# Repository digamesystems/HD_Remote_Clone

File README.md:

# HD Platinum Remote Clone

|  |  |
|:---:|:---:|
| Assembled (CAD render) | Exploded (CAD render) |

*The board inside, rev 1 (KiCad render). More in [hardware/](hardware/README.md).*

A DIY replacement for the handheld remote used with Hunter Douglas **Platinum Technology** motorized shades (the 2013-era system, before PowerView). It's built on an ESP32 with an IR LED (plus an IR receiver on the breadboard version, for capturing the original remote) and an nRF24L01+ 2.4 GHz radio.

> Personal hobby project. Not affiliated with or endorsed by Hunter Douglas. "Hunter Douglas", "Platinum" and "PowerView" are their trademarks and are used here only to say what this works with.

## Goal

Replace a degraded original remote with a homemade one that can:

- **Point and press (IR, 40 kHz):** control a single shade by aiming at its sensor eye. This is the arrows' default mode (red LED).
- **Group control (RF, 2.4 GHz):** pressing a group key (1–4 or ALL) opens a short window in which the arrows control that group over RF (green LED), as on the original.
- Run on batteries, sleeping deeply between presses and waking on a button press.

The protocols aren't documented, so the first phase was reverse engineering. This repo's firmware is the toolkit for that: it captures, dumps and replays IR, tests, scans and sniffs nRF24, and now drives shades on its own (IR with the RF wake, group commands, and pairing under its own ID). The next phase is the handheld: a custom PCB (designed, not yet built) and its firmware.

## Where things are

| Want to… | Go to |
|---|---|
| **Build one and control your shades** | **[docs/BUILD.md](docs/BUILD.md)** |
| Understand the IR codes | [docs/IR_PROTOCOL.md](docs/IR_PROTOCOL.md) |
| Understand the 2.4 GHz RF frames and pairing | [docs/RF_PROTOCOL.md](docs/RF_PROTOCOL.md) |
| See what is still unknown | [docs/RESEARCH.md](docs/RESEARCH.md) |
| See ideas beyond the stock remote | [docs/FEATURE_IDEAS.md](docs/FEATURE_IDEAS.md) |
| Run the firmware, see the serial commands and pin map | [docs/FIRMWARE.md](docs/FIRMWARE.md) |
| Wire the breadboard / nRF24 modules | [docs/WIRING.md](docs/WIRING.md) |
| Build the handheld | [docs/HARDWARE.md](docs/HARDWARE.md) (spec), [hardware/](hardware/README.md) (PCB), [hardware/enclosure/](hardware/enclosure/README.md) (case), [docs/BOM.md](docs/BOM.md), [docs/BRINGUP.md](docs/BRINGUP.md), [docs/COSTS.md](docs/COSTS.md) |
| Check the raw evidence | [captures/](captures/) (serial logs, logic-analyzer files; remote IDs redacted) |
| Test a change | [TESTING.md](TESTING.md) |

## Contributing

Hardware-independent logic belongs in `lib/hdcore/` with a host unit test; hardware-touching code goes in `src/`. Read [TESTING.md](TESTING.md) first. `include/hw_config.h` records what hardware is present on each board (breadboard, or the handheld PCB with `-e handheld`). Docs say what is confirmed and what is hypothesis; please keep it that way.

## Quick start

```
pio run -t upload         # breadboard (esp32dev)
pio device monitor        # 115200 baud, then type help
pio run -e handheld       # handheld PCB profile (builds; untested on hardware)
pio test -e native        # host unit tests, no hardware
```

Commands and pin map: [docs/FIRMWARE.md](docs/FIRMWARE.md).

## Status

| Stage | State |
|---|---|
| PlatformIO project, serial-menu firmware | ✅ builds |
| ESP32 board identified (DevKitC, WROOM-32D) | ✅ |
| IR protocol decoded (channel A: UP `0101`, DOWN `0110`; channel B: `1001` / `1010`), see [IR_PROTOCOL.md](docs/IR_PROTOCOL.md) | ✅ |
| IR transmit to a shade | ✅ works with our own RF wake, no original remote (2026-11-11); reliable at ~1 ft, range limited by IR aim/power. The shade sleeps after a few seconds, so the wake must keep coming through the press (2026-11-15) |
| nRF24 module screening (marked `NRF24L01+`, possibly clones) | ⏳ first module passes; rest to test |
| RF settings on our remotes | ✅ published settings confirmed by sniffing (2026-11-11) |
| RF wake frame for IR (`ID 01 00 80`) | ✅ sniffed from both remotes, see [RF_PROTOCOL.md](docs/RF_PROTOCOL.md) |
| RF transmit emulation | ✅ red-mode wake (`wake`, `send`) and group commands (`grp`): groups 1–4 and All, up and down (2026-11-11); group pairing under the clone's own ID (`pair`, 2026-11-12) |
| Handheld PCB (KiCad, [hardware/](hardware/README.md)) | ✅ schematic and layout complete, DRC/ERC clean; 5 assembled boards ordered from JLCPCB 2026-11-17, received 2026-11-25. ⏳ Bring-up under way: board 1 passes the unpowered, USB power and flashing stages; log in [docs/BRINGUP.md](docs/BRINGUP.md) |
| Enclosure (3D-printed clamshell, [hardware/enclosure/](hardware/enclosure/README.md)) | ✅ modelled, fit checks pass against the board; test print arrived 2026-11-20 and its values are in the model; the case order waits for the first board's measurements |
| Firmware pin profile for the PCB (`pio run -e handheld`) | ⏳ runs on board 1 (2026-11-25): serial menu, keys, A/B slider, radio and battery reading work (the voltage reads about 4.5 % high), and the board's keys move shades in group mode; indicator LED and IR not yet tested |
| Final remote: button UX, indicator LED, deep sleep, enclosure | ⏳ key logic written and host-tested, and running on the breadboard through the laptop keys (fw 0.9.11–0.9.12) and on the PCB through its own keys (fw 0.9.14); LED patterns and deep sleep still to be written |

## Technical approach
### What the original remote does

- **IR mode (red LED):** a proprietary IR code on a 40 kHz carrier, aimed at one shade. Pressing the opposite button stops movement.
- **RF mode (green LED):** an nRF24L01+ inside the remote. You select a group, then press OPEN or CLOSE within 5 s (we measured about 6.5 s; pressing a group key again restarts the window). Prior community work ([spitcool/hd-platinum-rf](https://github.com/spitcool/hd-platinum-rf), `docs/rf-protocol.md`, citing FCC filings, a register dump and SDR captures; and the [Arduino forum](https://forum.arduino.cc/t/nrf24l01-hack-on-hunter-douglas-shades/676940)) reports:

  | Parameter | Platinum handheld |
  |---|---|
  | Channels | 33, 52, 71 (2433 / 2452 / 2471 MHz), one packet per channel in rotation, for as long as the key is held |
  | Data rate | 2 Mbps |
  | Address | 3 bytes, `E7 E7 E7` (the nRF24 power-on default) |
  | Payload | 5 bytes, static: `ID0 ID1 MODE GROUP ACTION` |
  | CRC / auto-ack | CRC-16 / off |
  | Original TX power | about −6 dBm |

  - `ID0 ID1` identify the remote. Group commands are checked against the ID (a made-up ID gets no response), but the red-mode wake isn't (2026-11-12). Our two remotes have different IDs, and both work.
  - `MODE` is `20` with a group active, `01` for a red-mode press, and `30` / `31` for a setup-mode (pairing) add / remove. `GROUP` is `01/02/04/08` for groups 1–4, `FF` for All. `ACTION` is `A1` up held, `A2` down held, then `21` / `22` as a release tail; with the remote's A/B slider on B they are `A3` / `A4` and `23` / `24` (our sniff, 2026-11-25).
  - **A red-mode (IR) arrow press also sends RF:** `ID 01 00 80` while held, with no direction. The shade needs it before it will act on the IR. Our finding, 2026-11-11.
  - Example from the forum (another remote's ID): `03 C1 20 01 A1`, group 1 up.
  - Channel 7 / 1 Mbps, quoted in one forum thread, conflicts with this. spitcool's notes associate those settings with the later PowerView Pebble remote.
  - **Confirmed on both our remotes** by sniffing ch 33 (2026-11-11). Details in [RF_PROTOCOL.md](docs/RF_PROTOCOL.md).

Open questions and the reverse-engineering plan: [docs/RESEARCH.md](docs/RESEARCH.md).

## Hardware

Two targets. The **breadboard** was used for the reverse engineering and is what the [pin map](docs/FIRMWARE.md#pin-map) describes:

- **MCU:** ESP32-DevKitC with ESP32-WROOM-32D (PlatformIO `esp32dev`)
- **IR receive:** TSOP38238 (38 kHz part, fine for a 40 kHz remote at close range)
- **IR transmit:** TSAL6200 LED driven by an NPN transistor (2N2222) at ~100 mA pulses
- **RF:** nRF24L01+ module with a PCB antenna, 3.3 V supply and a 10 µF cap at the module

The **handheld PCB** (rev 1, DRC-clean; ordered from JLCPCB 2026-11-17, received 2026-11-25, in [bring-up](docs/BRINGUP.md)) has an ESP32-WROOM-32E, two TSAL6200 IR LEDs on constant-current sinks, no IR receiver, the nRF24 module in a low-profile 2×4 socket (Samtec SLW-104-01-G-D, with the module's header pins trimmed), seven keys plus a recessed SETUP button and an A/B channel slider, a red/green indicator LED seen through a light pipe, a LiPo cell charged over USB-C, and a USB-serial bridge for flashing and debugging. It lives in a 3D-printed clamshell case. See [docs/HARDWARE.md](docs/HARDWARE.md) (spec), [hardware/README.md](hardware/README.md) (layout status), [docs/BOM.md](docs/BOM.md) and [hardware/enclosure/](hardware/enclosure/README.md).

Pin map and firmware commands: [docs/FIRMWARE.md](docs/FIRMWARE.md). The handheld PCB uses a different pin map: see [docs/HARDWARE.md](docs/HARDWARE.md#pin-map-esp32-wroom-32e) and `include/pins.h`.

## Testing

```
pio test -e native                          # host unit tests, no hardware
pio test -e esp32dev_test --upload-port COM11    # on-device tests
```

See [TESTING.md](TESTING.md) for the three test tiers and the gate a release must pass.

## License

Copyright © 2026 John Price.

| Part | License |
|---|---|
| Firmware and tools (`src/`, `lib/`, `include/`, `test/`, `hardware/tools/`) | GNU General Public License, version 2 or (at your option) any later version (`GPL-2.0-or-later`). See [LICENSE](LICENSE). |
| Hardware design (`hardware/hd_remote/` KiCad files, `hardware/enclosure/` enclosure models) | CERN Open Hardware Licence v2, strongly reciprocal (`CERN-OHL-S-2.0`). See [hardware/LICENSE](hardware/LICENSE). |
| Documentation, captures and images (`docs/`, `captures/`, the READMEs) | Creative Commons Attribution-ShareAlike 4.0 (`CC-BY-SA-4.0`). See [docs/LICENSE](docs/LICENSE). |

Source files carry an `SPDX-License-Identifier` line. Third-party libraries keep their own licenses: [RF24](https://github.com/nRF24/RF24) (GPL-2.0) and [IRremoteESP8266](https://github.com/crankyoldgit/IRremoteESP8266) (LGPL-2.1). RF protocol facts credited to [spitcool/hd-platinum-rf](https://github.com/spitcool/hd-platinum-rf) are cited, not copied.

## Related projects

Found through [spitcool's CREDITS.md](https://github.com/spitcool/hd-platinum-rf/blob/main/CREDITS.md), which records the wider lineage in detail. Links checked 2026-11-18.

**Have the Platinum App Bridge?** These control Platinum shades through the Bridge over your LAN (TCP port 522), with no radio hardware to build:

- [node-hunterdouglas](https://github.com/exPHAT/node-hunterdouglas): JavaScript client, the earliest of these
- [homebridge-hunterdouglas-platinum](https://github.com/schemers/homebridge-hunterdouglas-platinum): Apple HomeKit via Homebridge
- [aio-powerrise-api](https://pypi.org/project/aio-powerrise-api/): asynchronous Python client
- [smartthings-hunterdouglasplatinum](https://github.com/schwark/smartthings-hunterdouglasplatinum): SmartThings integration
- [Platinum Shade Vera plug-in](https://community.ezlo.com/t/hunter-douglas-platinum-bridge-app/187439?page=3): Vera/Ezlo forum thread

**RF research and tools:**

- [spitcool/hd-platinum-rf](https://github.com/spitcool/hd-platinum-rf): SDR-based protocol research and an ESP32 bridge; the source of our RF air settings
- [gr-nrf24-sniffer](https://github.com/kittennbfive/gr-nrf24-sniffer): GNU Radio nRF24 receiver for an SDR such as a HackRF; supports 2 Mbps and 3-byte addresses (its own docs call 3-byte addresses untested)
- [gr-nordic](https://github.com/BastilleResearch/gr-nordic): GNU Radio Nordic ShockBurst receiver/transmitter (built around 5-byte addresses)
- [NRF24_Sniffer](https://github.com/Yveaux/NRF24_Sniffer): promiscuous sniffing with an nRF24 module

**Other Platinum devices** (FCC IDs; descriptions from spitcool's notes): [UXURC4U](https://fccid.io/UXURC4U) handheld remote, [UXURC4U2](https://fccid.io/UXURC4U2) handheld remote (ours), [UXURC4U3](https://fccid.io/UXURC4U3) later handheld remote, [UXUWS4U](https://fccid.io/UXUWS4U) wall switch. Only the UXURC4U2 has been tested with this project.

**Not compatible:** Hunter Douglas says current PowerView remotes and accessories, such as the Pebble, use a different communication method from Platinum Technology products and can't control older shades ([FAQ](https://www.hunterdouglas.com/faqs/can-i-use-my-new-powerview-pebble-remote-to-operate-my-older-powerrise-shades)).

## References

- [NRF24L01+ hack on Hunter Douglas shades](https://forum.arduino.cc/t/nrf24l01-hack-on-hunter-douglas-shades/676940) (Arduino forum)
- [ESP8266 and NRF24L01+ Hunter Douglas Platinum Remote](https://forum.arduino.cc/t/esp8266-and-nrf24l01-hunter-douglas-platinum-remote/918887) (Arduino forum)
- [spitcool/hd-platinum-rf](https://github.com/spitcool/hd-platinum-rf): protocol research
- [Platinum Technology remote guide (PDF)](https://blindparts.com/wp-content/uploads/1970/01/Hunter-Douglas-Platinum-Technology-Remote-Control-Guide.pdf)
- [Bond forum: IR replay attempts / RF wake theory](https://forum.bondhome.io/t/hunterdouglas-powerrise-2-0-with-platinum-technology/3050)
- [AVS forum: automating PowerRise (2007)](https://www.avsforum.com/threads/automating-hunter-douglas-powerrise.852487/)

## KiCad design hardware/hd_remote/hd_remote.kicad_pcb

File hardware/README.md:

# Hardware

*Rev 1 as ordered 2026-11-17: KiCad 3D render, not a photo. Top side, front (IR) end at the right. Some 3D models are stand-ins (the IR LEDs render green, the indicator white).*

KiCad project for the handheld replacement remote: [`hd_remote/hd_remote.kicad_pro`](hd_remote/hd_remote.kicad_pro).

- **Tool:** KiCad 10 (the files open in 9.0 or newer).
- **Spec:** [docs/HARDWARE.md](../docs/HARDWARE.md) holds the design decisions, pin map, power budget and open questions. Change the spec first, then the schematic.
- **Breadboard wiring** (the DevKitC prototype this board replaces): [docs/WIRING.md](../docs/WIRING.md).

## Status

| Sheet | State |
|---|---|
| Power and USB (`power_usb.kicad_sch`) | complete, drafted 2026-11-12. Values and *verify* items: [docs/HARDWARE.md](../docs/HARDWARE.md#schematic-power-and-usb-sheet-draft-2026-11-12) |
| MCU (`mcu.kicad_sch`) | complete, drafted 2026-11-12: [docs/HARDWARE.md](../docs/HARDWARE.md#schematic-mcu-sheet-draft-2026-11-12) |
| IR (`ir.kicad_sch`) | complete, drafted 2026-11-12: [docs/HARDWARE.md](../docs/HARDWARE.md#schematic-ir-sheet-draft-2026-11-12) |
| nRF24 (`nrf24.kicad_sch`), Buttons and LEDs (`ui.kicad_sch`) | complete, drafted 2026-11-12: [docs/HARDWARE.md](../docs/HARDWARE.md#schematic-nrf24-and-buttonsleds-sheets-draft-2026-11-12) |
| Test and debug (`test.kicad_sch`) | complete, drafted 2026-11-12: [docs/HARDWARE.md](../docs/HARDWARE.md#test-points-2026-11-12). Test points on nets local to other sheets live on those sheets |
| Layout | started 2026-11-13: all 109 footprints and 82 nets pulled in from the schematic (DRC schematic parity: 0 issues), parked below the sheet. Board outline (145.45 × 40.45 mm) from `docs/images/enclosure/enclosure_pcb_outline.dxf`, board centre at (100, 80) mm on the sheet, front end (IR LEDs) at +X, top view not mirrored; M2 holes H601–H604 placed and locked at (±61, ±15.5) mm. Design rules: KiCad defaults, inside JLC's standard process (0.2 mm track/clearance, 0.3 mm min hole). **U201 is modified locally:** its 12 ground-pad vias are 0.3 mm drill / 0.6 mm pad (the library has 0.2 mm, below JLC's standard drill), so DRC reports one expected `lib_footprint_mismatch`; don't update U201 from the library. **Case-fixed parts placed and locked** (2026-11-13) from `hardware/enclosure` coordinates: 7 key switches, SETUP (underside, 22 mm from the front, 10 mm right of centre), IR LEDs D303/D304, indicator D501, A/B SW509, USB-C J101, battery JST J102, ESP32 U201, nRF24 socket J401. Keep-outs: battery (named rule area `Battery` + custom rule in `hd_remote.kicad_dru`: no THT component pins over the cell; plated vias allowed), bottom side under each key's support pad, screw heads/standoffs, and the nRF24 module's PCB antenna. Expected DRC: silkscreen clipped at the board edge where the LEDs, USB-C and JST overhang it. **Rest of the parts: first-pass placement** (2026-11-13, scripted, unlocked): each part at the nearest free spot to the pads it connects to, ICs first; no courtyard or keep-out errors. It proves the fit, not a final layout: move decoupling caps to their pins (C201 especially), tighten the USB pair, tidy the silkscreen. **Check before routing:** J401's pin-1 orientation against a real module. **First-draft placement complete** (2026-11-13, by hand): every part on the board, DRC errors 0. **Routing setup** (2026-11-13): net classes Power 0.5 mm (+3V3, VBUS, NRF_VCC) and HighCurrent 0.6 mm (VBAT, VBAT_BATT, VBAT_JP, IR_K1/K2, IR_E1/E2; 0.6 matches the SOT-23 pads and carries well over the ~300 mA peak), Default 0.2 mm; GND pour on B.Cu over the whole board (0.3 mm clearance, thermal reliefs), kept out of both antenna keep-outs and the screw heads. **ESP32 rotated 180°** (2026-11-13): antenna end at the −Y edge, so its key/RTC pins face the keys and its SPI/UART pins face the back (see docs/HARDWARE.md, Layout notes); 21 parts re-homed (EN, battery-sense and 3V3 decoupling to the new pin positions; BOOT, J601, JP101/Q103, charger caps and the underside test pads out of the module's new footprint and antenna keep-out); case model updated, 51/51 checks pass. **Power path added** (2026-11-13, Microchip AN1149): D102 STPS1H100AY, Q104 AO3401A, R114 100 kΩ, TP102; loads (LDO, IR LEDs) moved from VBAT to the new VSYS rail; schematic ERC 0, board synced (parity 0), new parts placed by the charger. **Routing complete** (2026-11-14, by hand): DRC 0 errors, **0 unconnected**, schematic parity clean; ERC 0. Expected DRC warnings only: silkscreen clipped at the board edge (J101, J102, D303, D304); the other silkscreen warnings were tidied 2026-11-16; and U201's `lib_footprint_mismatch`. Decisions made while routing: the nRF24 antenna rule area bans ground fill and pads but allows tracks and vias (docs/HARDWARE.md, nRF24 socket); GND pour on B.Cu only, stitched; **VSYS** runs from D102/Q104 along the board's north edge to the IR stage, and U104 is fed from there along the existing y 85.5 run (about 200 mm of 0.6 mm track to the LDO: a few mV of drop, 20–30 mV of IR-burst ripple at its input); +3V3 to the nRF supply (FB401) along the top edge; **SW202 has "duplicate pad numbers are jumpers" set** (its two IO0 pads are joined inside the switch, and the second pad sits beyond a +3V3 track). Set it on the schematic's `Switch:SW_Push` symbol in `mcu.kicad_sch` (so SW201 has it too), not just on the footprint: Update PCB from Schematic copies the symbol's setting and reset the footprint-only fix on 2026-11-15; a small GND patch near SW202 is tied to the main plane through SW202's GND pad. **Since then (2026-11-16):** silkscreen tidied; board STEP exported and clash-checked against the case (61 checks); **J401 footprint fixed** (KiCad's `PinSocket_2x04` mirrors the pad order, so the module's pins were swapped between columns; now `PinHeader_2x04` at the same holes, re-routed); the ground pour opened around J401's GND pin (NRF_IRQ_OPT moved to the top layer beside it); J401 is a Samtec SLW-104-01-G-D. DRC 0 errors, 0 unconnected, schematic parity 0. **Ordered from JLCPCB on 2026-11-17** (5 assembled); the order record and what the dry run found are in [docs/BRINGUP.md](../docs/BRINGUP.md), Order log |

Synced with the enclosure (2026-11-13): mounting holes H601–H604 (M2), key switch MPNs (Same Sky TS02), nRF24 socket on J401 (Samtec SLW-104-01-G-D from 2026-11-16).

**Firmware pin map check:** `python -I hardware/tools/check_pins.py` (from the repo root) exports the schematic netlist and confirms every `PIN_` constant in the handheld block of `include/pins.h` is on the right ESP32 net, and that no ESP32 signal net is missing from it. Run it after any change to the MCU sheet or `pins.h`; it exits 1 on a mismatch.

**Footprint settings check:** `python -I hardware/tools/check_fp_overrides.py` compares every footprint's per-board settings (locked, attributes such as DNP and exclude-from-BOM, the duplicate-pads-are-jumpers and net-tie settings, local clearance/mask/paste/zone overrides) with the committed baseline `hd_remote/fp_overrides.json`. Run it after every Update PCB from Schematic (F8) or footprint swap: F8 silently reset SW202's jumper setting once. If a change is intended, `--update` and commit the baseline with the board.

**Bring-up:** the staged plan for the first boards is [docs/BRINGUP.md](../docs/BRINGUP.md).

**Fab files for JLCPCB:** `python -I hardware/tools/make_jlc.py` (from the repo root) writes `hardware/fab/`: a Gerber zip (Protel extensions, Excellon drill with PTH and NPTH separate, top-side assembly), a JLC BOM and a JLC placement (CPL) file. The BOM lists only the parts JLC assembles (an LCSC number, not DNP, not through-hole; use `--tht J102` to have JLC place a through-hole part). The CPL keeps KiCad's rotations, so check polarized parts in JLC's placement preview. Rerun it after any board or schematic change.

**Parts list:** [docs/BOM.md](../docs/BOM.md). Its board table is generated from the schematic by `hardware/tools/make_bom.py` (LCSC details cached in `hardware/bom/lcsc_cache.json`, fetched by `lcsc_fetch.py`); rerun it after any schematic change.

ERC (2026-11-13, rechecked 2026-11-16): **0 errors, 0 warnings** on the whole design. References are numbered by sheet: 1xx Power and USB, 2xx MCU, 3xx IR, 4xx nRF24, 5xx Buttons and LEDs, 6xx Test and debug.

## Generator scripts

`tools/` holds the Python scripts that drew the first drafts (`gen_power_usb.py`, `gen_mcu.py`, `gen_ir.py`, `gen_nrf24.py`, `gen_ui.py`, `gen_test.py`, using `schgen.py` and `sexpr.py`). They pull symbols from the installed KiCad 10 libraries and connect every pin to a net label, so connectivity is by name. **Once a sheet has been edited in KiCad, the KiCad file is the master**: don't rerun its generator over it.

    python -I hardware/tools/gen_power_usb.py
    python -I hardware/tools/gen_mcu.py
    python -I hardware/tools/gen_ir.py
    python -I hardware/tools/gen_nrf24.py
    python -I hardware/tools/gen_ui.py
    python -I hardware/tools/gen_test.py

The KiCad library path is set at the top of `tools/sexpr.py`, or with the `KICAD_SYMBOL_DIR` environment variable.

## Conventions

- Local KiCad state (`*.kicad_prl`), backups and caches are git-ignored. Commit the `.kicad_pro`, `.kicad_sch` and `.kicad_pcb` files, plus any project-specific symbol and footprint libraries.
- Parts should come with an LCSC number where possible, so JLC assembly stays an option.
- **License:** the KiCad design is CERN-OHL-S-2.0 ([LICENSE](LICENSE)); the generator scripts in `tools/` are GPL-2.0-or-later, like the firmware.

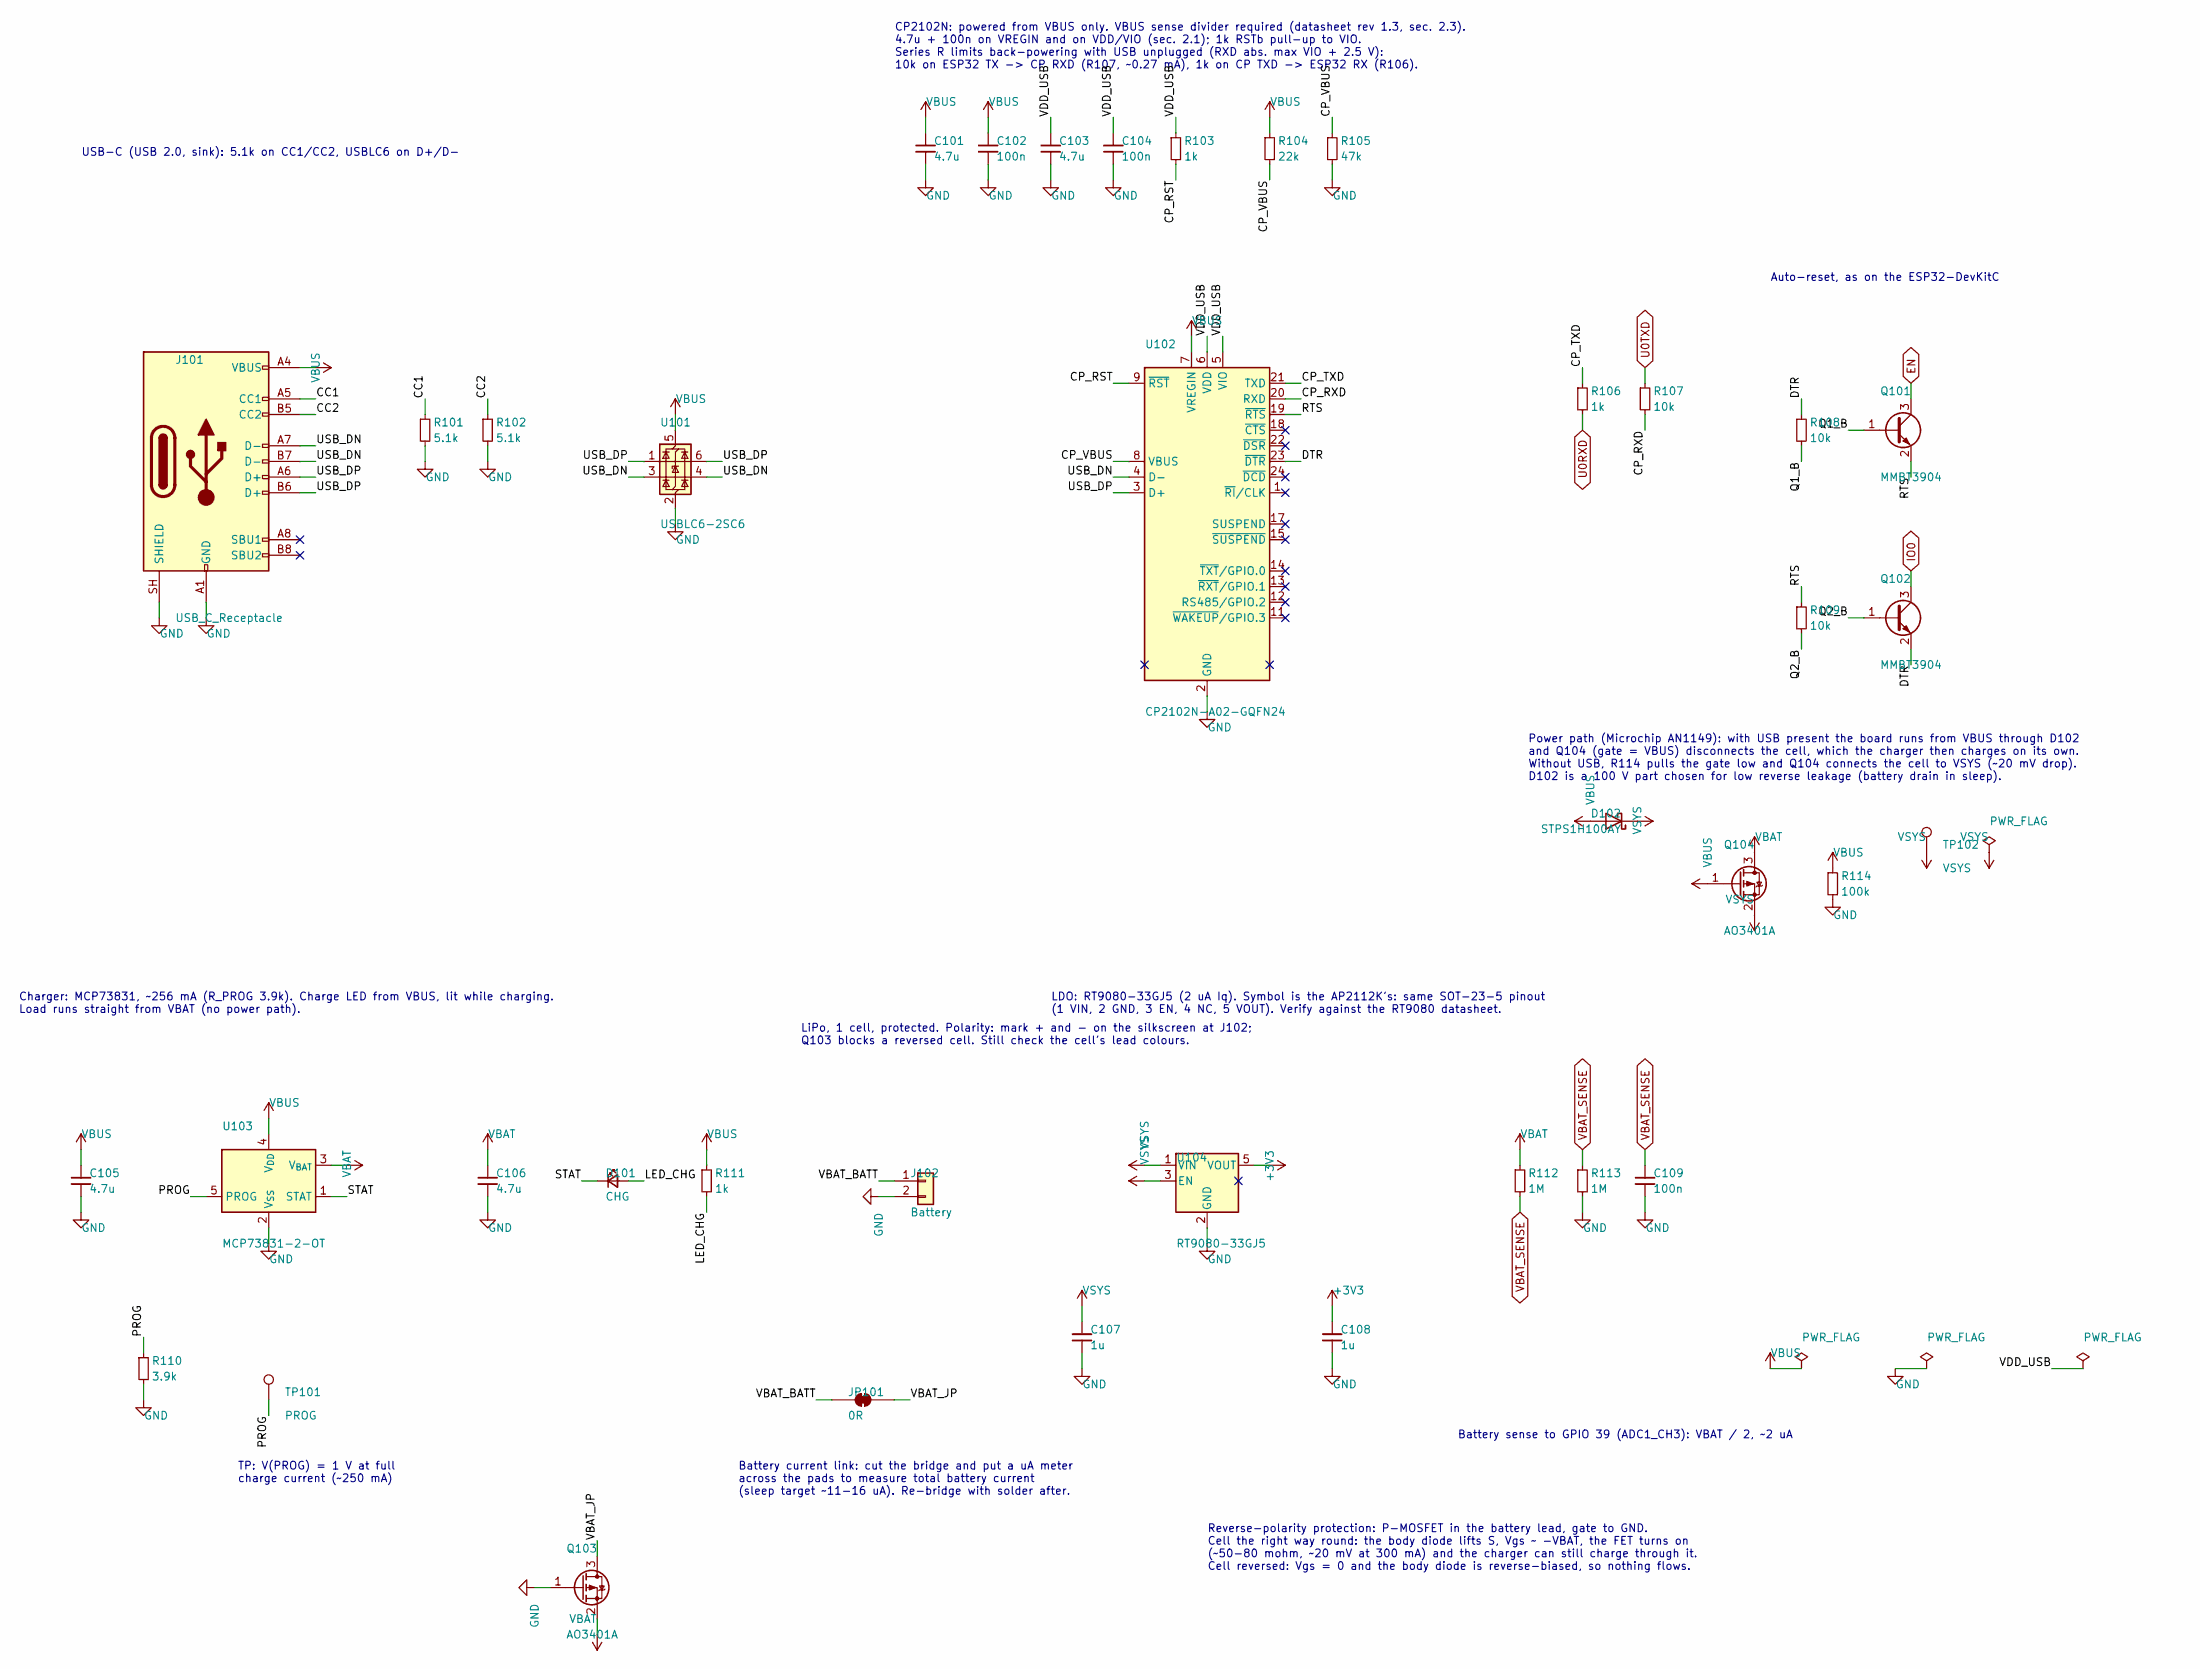
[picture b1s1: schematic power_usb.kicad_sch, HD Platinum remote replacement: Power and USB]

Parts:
C101, C103, C105, C106: 4.7u; C_0603_1608Metric; LCSC C19666
C102, C104, C109: 100n; C_0603_1608Metric; LCSC C14663
C107, C108: 1u; C_0603_1608Metric; LCSC C15849
D101: CHG; LED_Kingbright_APA1606_1.6x0.6mm_Horizontal; LCSC C3034753
D102: STPS1H100AY; D_SMA; MPN STPS1H100AY; LCSC C181833
J101: USB_C_Receptacle; USB_C_Receptacle_HRO_TYPE-C-31-M-12; LCSC C165948
J102: Battery; JST_PH_S2B-PH-K_1x02_P2.00mm_Horizontal; LCSC C173752
JP101: 0R; R_0805_2012Metric; LCSC C17477
Q101, Q102: MMBT3904; SOT-23; LCSC C20526
Q103, Q104: AO3401A; SOT-23; LCSC C15127
R101, R102: 5.1k; R_0603_1608Metric; LCSC C23186
R103, R106, R111: 1k; R_0603_1608Metric; LCSC C21190
R104: 22k; R_0603_1608Metric; LCSC C31850
R105: 47k; R_0603_1608Metric; LCSC C25819
R107, R108, R109: 10k; R_0603_1608Metric; LCSC C25804
R110: 3.9k; R_0603_1608Metric; LCSC C23018
R112, R113: 1M; R_0603_1608Metric; LCSC C22935
R114: 100k; R_0603_1608Metric; LCSC C25803
TP101: PROG; TestPoint_Pad_D1.5mm
TP102: VSYS; TestPoint_Pad_D1.5mm
U101: USBLC6-2SC6; SOT-23-6; LCSC C7519
U102: CP2102N-A02-GQFN24; QFN-24-1EP_4x4mm_P0.5mm_EP2.6x2.6mm; LCSC C969151
U103: MCP73831-2-OT; SOT-23-5; LCSC C424093
U104: RT9080-33GJ5; SOT-23-5; LCSC C841192

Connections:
+3V3: C108.1, U104.5 (VOUT); also elsewhere on the board
/Power and USB/CC1: J101.A5 (CC1), R101.1
/Power and USB/CC2: J101.B5 (CC2), R102.1
/Power and USB/CP_RST: R103.2, U102.9 (~RST)
/Power and USB/CP_RXD: R107.2, U102.20 (RXD)
/Power and USB/CP_TXD: R106.1, U102.21 (TXD)
/Power and USB/CP_VBUS: R104.2, R105.1, U102.8 (VBUS)
/Power and USB/DTR: Q102.2 (E), R108.1, U102.23 (~DTR)
/Power and USB/LED_CHG: D101.2 (A), R111.2
/Power and USB/PROG: R110.1, TP101.1 (1_1), U103.5 (PROG)
/Power and USB/Q1_B: Q101.1 (B), R108.2
/Power and USB/Q2_B: Q102.1 (B), R109.2
/Power and USB/RTS: Q101.2 (E), R109.1, U102.19 (~RTS)
/Power and USB/STAT: D101.1 (K), U103.1 (STAT)
/Power and USB/USB_DN: J101.A7 (D-), J101.B7 (D-), U101.3 (I/O2), U101.4 (I/O2), U102.4 (D-)
/Power and USB/USB_DP: J101.A6 (D+), J101.B6 (D+), U101.1 (I/O1), U101.6 (I/O1), U102.3 (D+)
/Power and USB/VBAT_BATT: J102.1, JP101.1 (A)
/Power and USB/VBAT_JP: JP101.2 (B), Q103.3 (D)
/Power and USB/VDD_USB: C103.1, C104.1, R103.1, U102.5 (VIO), U102.6 (VDD)
EN: Q101.3 (C); also elsewhere on the board
GND: C101.2, C102.2, C103.2, C104.2, C105.2, C106.2, C107.2, C108.2, C109.2, J101.A1 (GND), J101.A12 (GND), J101.B1 (GND), J101.B12 (GND), J101.SH (SHIELD), J102.2, Q103.1 (G), R101.2, R102.2, R105.2, R110.2, R113.2, R114.2, U101.2 (GND), U102.2 (GND), U102.25 (GND), U103.2 (V_{SS}), U104.2 (GND); also elsewhere on the board
IO0: Q102.3 (C); also elsewhere on the board
U0RXD: R106.2; also elsewhere on the board
U0TXD: R107.1; also elsewhere on the board
VBAT: C106.1, Q103.2 (S), Q104.3 (D), R112.1, U103.3 (V_{BAT}); also elsewhere on the board
VBAT_SENSE: C109.1, R112.2, R113.1; also elsewhere on the board
VBUS: C101.1, C102.1, C105.1, D102.2 (A), J101.A4 (VBUS), J101.A9 (VBUS), J101.B4 (VBUS), J101.B9 (VBUS), Q104.1 (G), R104.1, R111.1, R114.1, U101.5 (VBUS), U102.7 (VREGIN), U103.4 (V_{DD}); also elsewhere on the board
VSYS: C107.1, D102.1 (K), Q104.2 (S), TP102.1 (1_1), U104.1 (VIN), U104.3 (EN); also elsewhere on the board

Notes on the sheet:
Reverse-polarity protection: P-MOSFET in the battery lead, gate to GND. Cell the right way round: the body diode lifts S, Vgs ~ -VBAT, the FET turns on (~50-80 mohm, ~20 mV at 300 mA) and the charger can still charge through it. Cell reversed: Vgs = 0 and the body diode is reverse-biased, so nothin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
Battery current link: cut the bridge and put a uA meter across the pads to measure total battery current (sleep target ~11-16 uA). Re-bridge with solder after.
CP2102N: powered from VBUS only. VBUS sense divider required (datasheet rev 1.3, sec. 2.3). 4.7u + 100n on VREGIN and on VDD/VIO (sec. 2.1); 1k RSTb pull-up to VIO. Series R limits back-powering with USB unplugged (RXD abs. max VIO + 2.5 V): 10k on ESP32 TX -> CP RXD (R107, ~0.27 mA), 1k on CP TXD 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
Auto-reset, as on the ESP32-DevKitC
Charger: MCP73831, ~256 mA (R_PROG 3.9k). Charge LED from VBUS, lit while charging. Load runs straight from VBAT (no power path).
Power path (Microchip AN1149): with USB present the board runs from VBUS through D102 and Q104 (gate = VBUS) disconnects the cell, which the charger then charges on its own. Without USB, R114 pulls the gate low and Q104 connects the cell to VSYS (~20 mV drop). D102 is a 100 V part chosen for low re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
USB-C (USB 2.0, sink): 5.1k on CC1/CC2, USBLC6 on D+/D-
LiPo, 1 cell, protected. Polarity: mark + and - on the silkscreen at J102; Q103 blocks a reversed cell. Still check the cell's lead colours.
Battery sense to GPIO 39 (ADC1_CH3): VBAT / 2, ~2 uA
LDO: RT9080-33GJ5 (2 uA Iq). Symbol is the AP2112K's: same SOT-23-5 pinout (1 VIN, 2 GND, 3 EN, 4 NC, 5 VOUT). Verify against the RT9080 datasheet.
TP: V(PROG) = 1 V at full charge current (~250 mA)

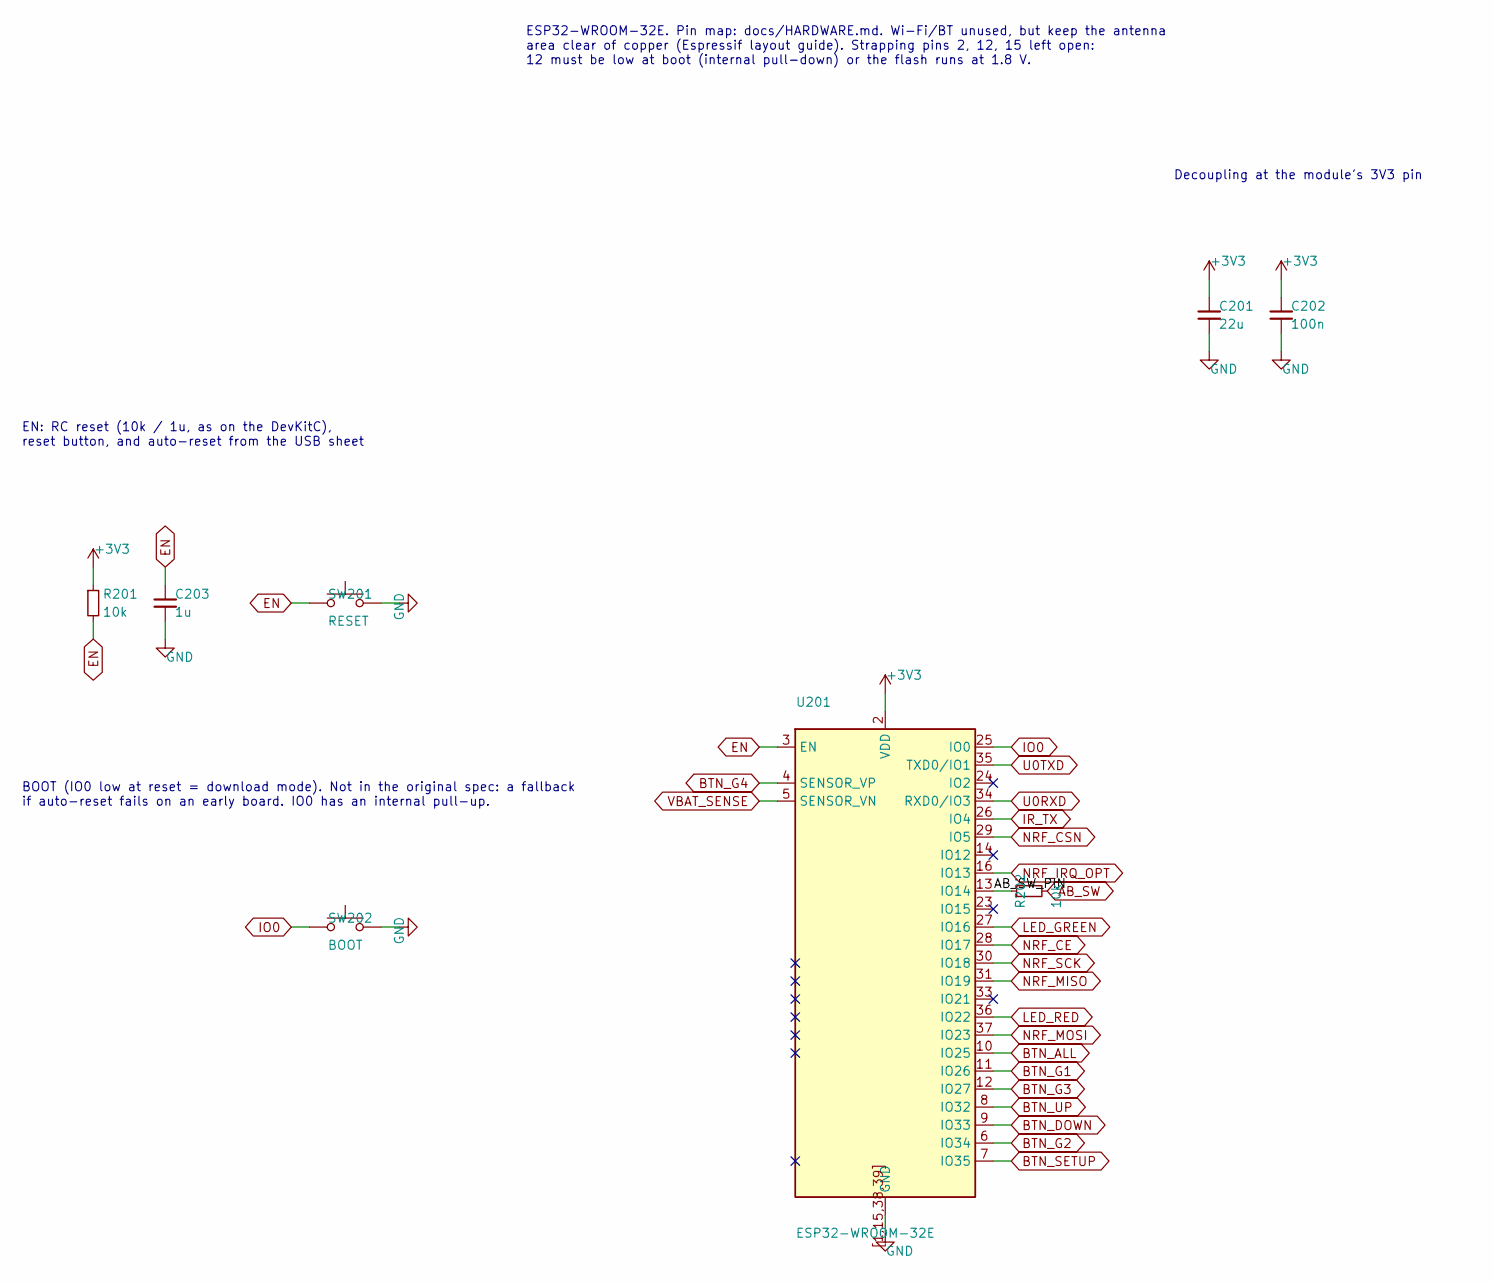
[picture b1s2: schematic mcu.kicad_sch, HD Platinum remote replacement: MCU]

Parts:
C201: 22u; C_0805_2012Metric; LCSC C45783
C202: 100n; C_0603_1608Metric; LCSC C14663
C203: 1u; C_0603_1608Metric; LCSC C15849
R201, R202: 10k; R_0603_1608Metric; LCSC C25804
SW201: RESET; SW_Push_1P1T_NO_CK_KMR2; LCSC C269272
SW202: BOOT; SW_Push_1P1T_NO_CK_KMR2; LCSC C269272
U201: ESP32-WROOM-32E; LCSC C701341

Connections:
+3V3: C201.1, C202.1, R201.1, U201.2 (VDD); also elsewhere on the board
/MCU/AB_SW_PIN: R202.1, U201.13 (IO14)
AB_SW: R202.2; also elsewhere on the board
BTN_ALL: U201.10 (IO25); also elsewhere on the board
BTN_DOWN: U201.9 (IO33); also elsewhere on the board
BTN_G1: U201.11 (IO26); also elsewhere on the board
BTN_G2: U201.6 (IO34); also elsewhere on the board
BTN_G3: U201.12 (IO27); also elsewhere on the board
BTN_G4: U201.4 (SENSOR_VP); also elsewhere on the board
BTN_SETUP: U201.7 (IO35); also elsewhere on the board
BTN_UP: U201.8 (IO32); also elsewhere on the board
EN: C203.1, R201.2, SW201.1, U201.3 (EN); also elsewhere on the board
GND: C201.2, C202.2, C203.2, SW201.2, SW202.2, U201.1 (GND), U201.15 (GND), U201.38 (GND), U201.39 (GND), U201.[1,15,38,39] (GND); also elsewhere on the board
IO0: SW202.1, U201.25 (IO0); also elsewhere on the board
IR_TX: U201.26 (IO4); also elsewhere on the board
LED_GREEN: U201.27 (IO16); also elsewhere on the board
LED_RED: U201.36 (IO22); also elsewhere on the board
NRF_CE: U201.28 (IO17); also elsewhere on the board
NRF_CSN: U201.29 (IO5); also elsewhere on the board
NRF_IRQ_OPT: U201.16 (IO13); also elsewhere on the board
NRF_MISO: U201.31 (IO19); also elsewhere on the board
NRF_MOSI: U201.37 (IO23); also elsewhere on the board
NRF_SCK: U201.30 (IO18); also elsewhere on the board
U0RXD: U201.34 (RXD0/IO3); also elsewhere on the board
U0TXD: U201.35 (TXD0/IO1); also elsewhere on the board
VBAT_SENSE: U201.5 (SENSOR_VN); also elsewhere on the board

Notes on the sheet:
EN: RC reset (10k / 1u, as on the DevKitC), reset button, and auto-reset from the USB sheet
Decoupling at the module's 3V3 pin
BOOT (IO0 low at reset = download mode). Not in the original spec: a fallback if auto-reset fails on an early board. IO0 has an internal pull-up.
ESP32-WROOM-32E. Pin map: docs/HARDWARE.md. Wi-Fi/BT unused, but keep the antenna area clear of copper (Espressif layout guide). Strapping pins 2, 12, 15 left open: 12 must be low at boot (internal pull-down) or the flash runs at 1.8 V.

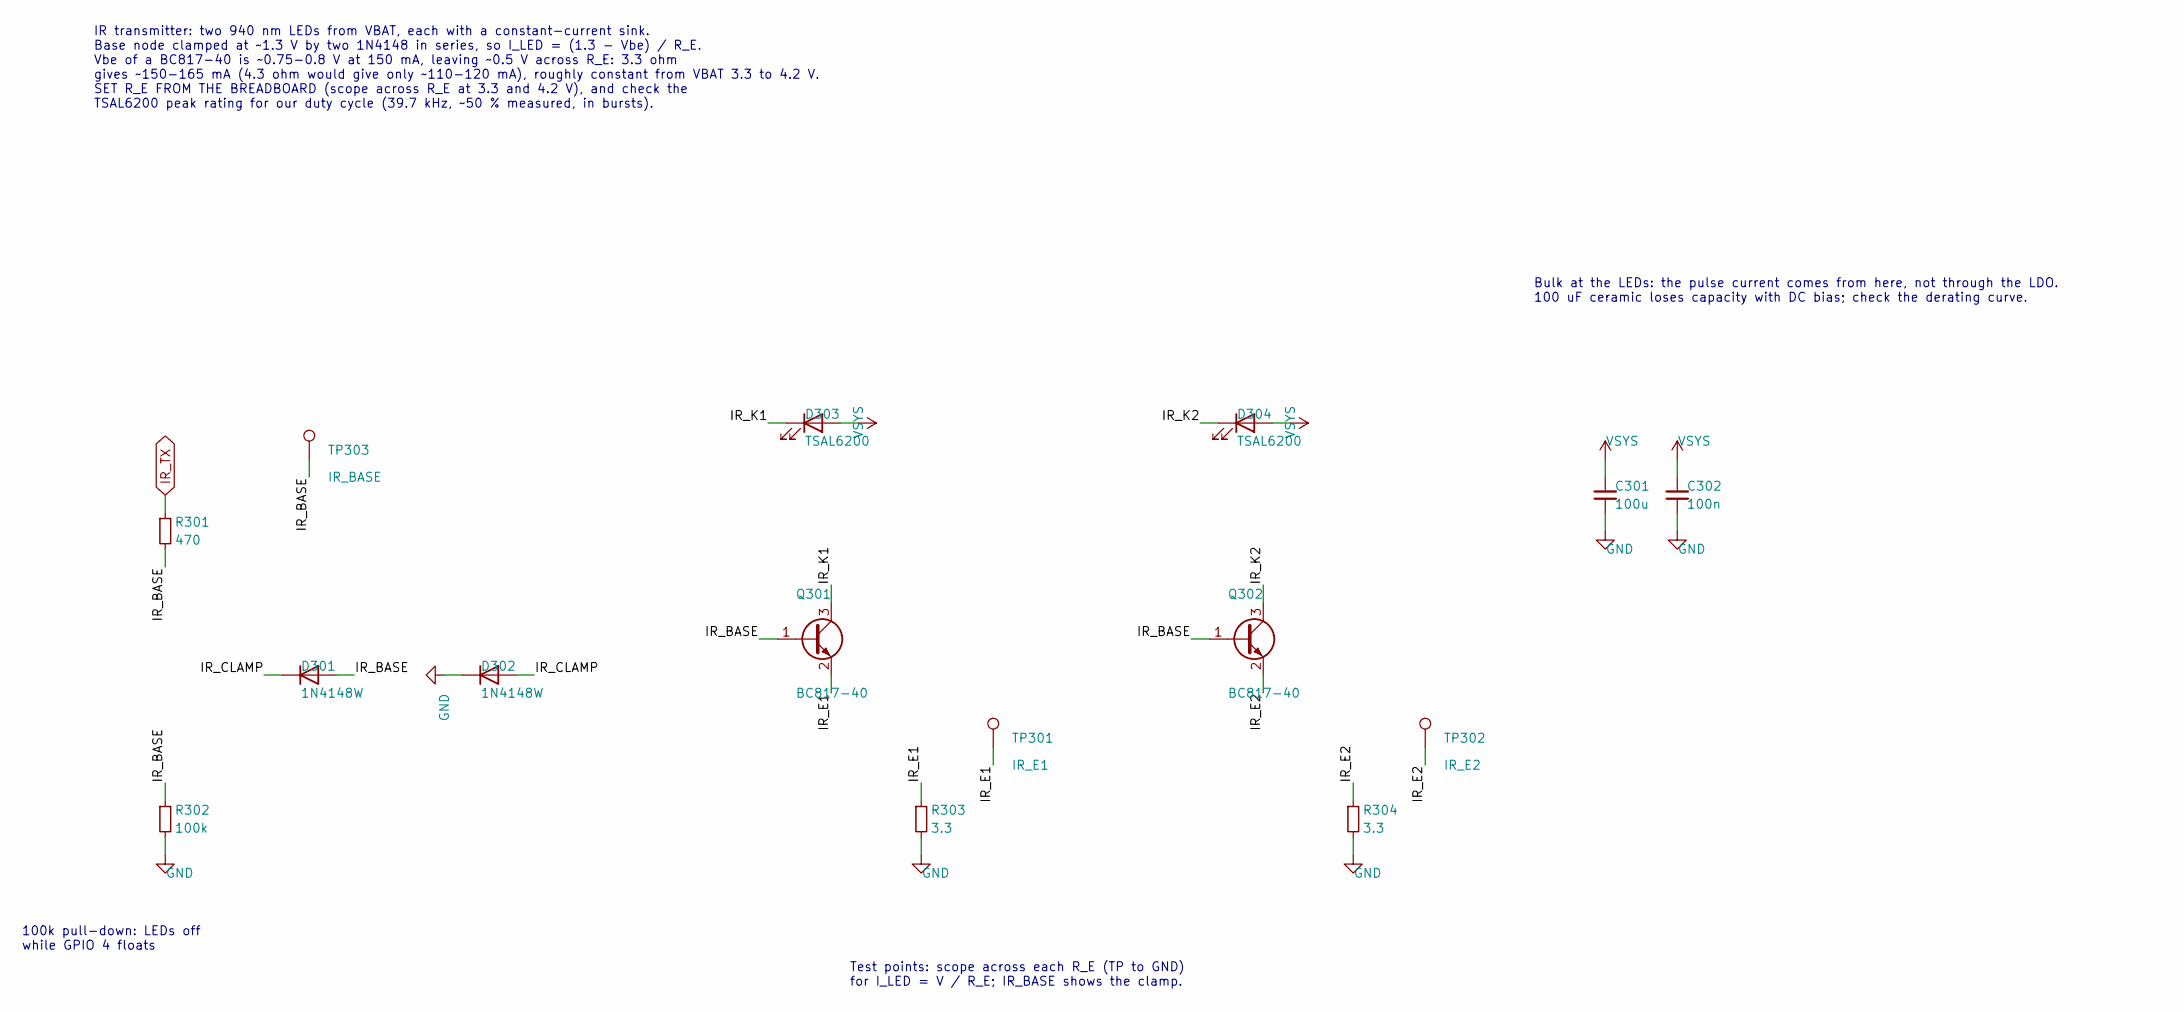
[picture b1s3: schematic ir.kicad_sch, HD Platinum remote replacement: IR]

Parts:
C301: 100u; C_1206_3216Metric; LCSC C15008
C302: 100n; C_0603_1608Metric; LCSC C14663
D301, D302: 1N4148W; D_SOD-123; LCSC C81598
D303, D304: TSAL6200; LED_D5.0mm_Horizontal_O1.27mm_Z3.0mm; MPN TSAL6200
Q301, Q302: BC817-40; SOT-23; LCSC C52801
R301: 470; R_0603_1608Metric; LCSC C23179
R302: 100k; R_0603_1608Metric; LCSC C25803
R303, R304: 3.3; R_0805_2012Metric; LCSC C2907250
TP301: IR_E1; TestPoint_Pad_D1.5mm
TP302: IR_E2; TestPoint_Pad_D1.5mm
TP303: IR_BASE; TestPoint_Pad_D1.5mm

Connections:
/IR/IR_BASE: D301.2 (A), Q301.1 (B), Q302.1 (B), R301.2, R302.1, TP303.1 (1_1)
/IR/IR_CLAMP: D301.1 (K), D302.2 (A)
/IR/IR_E1: Q301.2 (E), R303.1, TP301.1 (1_1)
/IR/IR_E2: Q302.2 (E), R304.1, TP302.1 (1_1)
/IR/IR_K1: D303.1 (K), Q301.3 (C)
/IR/IR_K2: D304.1 (K), Q302.3 (C)
GND: C301.2, C302.2, D302.1 (K), R302.2, R303.2, R304.2; also elsewhere on the board
IR_TX: R301.1; also elsewhere on the board
VSYS: C301.1, C302.1, D303.2 (A), D304.2 (A); also elsewhere on the board

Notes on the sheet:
100k pull-down: LEDs off while GPIO 4 floats
IR transmitter: two 940 nm LEDs from VBAT, each with a constant-current sink. Base node clamped at ~1.3 V by two 1N4148 in series, so I_LED = (1.3 - Vbe) / R_E. Vbe of a BC817-40 is ~0.75-0.8 V at 150 mA, leaving ~0.5 V across R_E: 3.3 ohm gives ~150-165 mA (4.3 ohm would give only ~110-120 mA), ro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
Test points: scope across each R_E (TP to GND) for I_LED = V / R_E; IR_BASE shows the clamp.
Bulk at the LEDs: the pulse current comes from here, not through the LDO. 100 uF ceramic loses capacity with DC bias; check the derating curve.

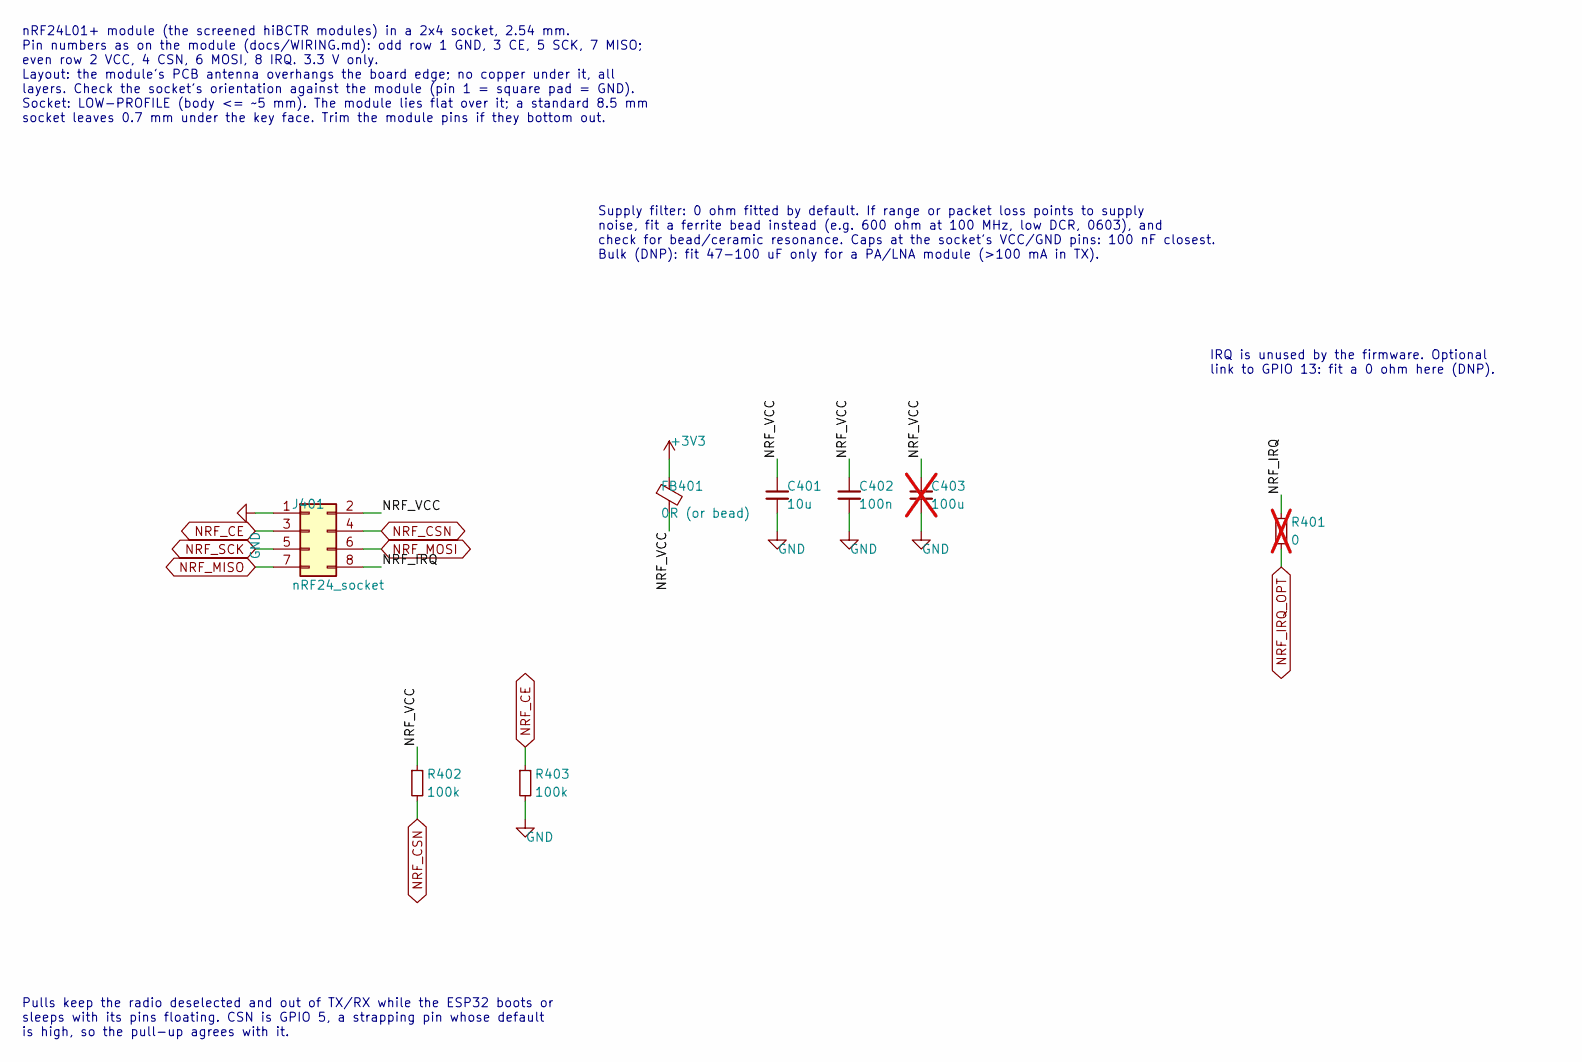
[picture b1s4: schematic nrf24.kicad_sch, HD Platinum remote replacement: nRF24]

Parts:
C401: 10u; C_0805_2012Metric; LCSC C15850
C402: 100n; C_0603_1608Metric; LCSC C14663
C403: 100u; C_1206_3216Metric; LCSC C15008; not fitted
FB401: 0R (or bead); L_0603_1608Metric; LCSC C21189
J401: nRF24_socket; PinHeader_2x04_P2.54mm_Vertical; MPN SLW-104-01-G-D
R401: 0; R_0603_1608Metric; LCSC C21189; not fitted
R402, R403: 100k; R_0603_1608Metric; LCSC C25803

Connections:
+3V3: FB401.1; also elsewhere on the board
/nRF24/NRF_IRQ: J401.8, R401.1
/nRF24/NRF_VCC: C401.1, C402.1, C403.1, FB401.2, J401.2, R402.1
GND: C401.2, C402.2, C403.2, J401.1, R403.2; also elsewhere on the board
NRF_CE: J401.3, R403.1; also elsewhere on the board
NRF_CSN: J401.4, R402.2; also elsewhere on the board
NRF_IRQ_OPT: R401.2; also elsewhere on the board
NRF_MISO: J401.7; also elsewhere on the board
NRF_MOSI: J401.6; also elsewhere on the board
NRF_SCK: J401.5; also elsewhere on the board

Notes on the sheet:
IRQ is unused by the firmware. Optional link to GPIO 13: fit a 0 ohm here (DNP).
Supply filter: 0 ohm fitted by default. If range or packet loss points to supply noise, fit a ferrite bead instead (e.g. 600 ohm at 100 MHz, low DCR, 0603), and check for bead/ceramic resonance. Caps at the socket's VCC/GND pins: 100 nF closest. Bulk (DNP): fit 47-100 uF only for a PA/LNA module (>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
Pulls keep the radio deselected and out of TX/RX while the ESP32 boots or sleeps with its pins floating. CSN is GPIO 5, a strapping pin whose default is high, so the pull-up agrees with it.
nRF24L01+ module (the screened hiBCTR modules) in a 2x4 socket, 2.54 mm. Pin numbers as on the module (docs/WIRING.md): odd row 1 GND, 3 CE, 5 SCK, 7 MISO; even row 2 VCC, 4 CSN, 6 MOSI, 8 IRQ. 3.3 V only. Layout: the module's PCB antenna overhangs the board edge; no copper under it, all layers. Ch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
